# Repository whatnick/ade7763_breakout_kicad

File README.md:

# ADE7763 Breakout

Minimal Breakout Board for Analog Devices [ADE7763](https://www.analog.com/media/en/technical-documentation/data-sheets/ADE7763.pdf) Enegry Monitor ASIC. This ASIC is a bit dated, but well supported and heavily used in commercial/off-the-shelf
energy metering devices.

## Where to get it

This breakout can be obtained on:
-  [Tindie](https://www.tindie.com/products/whatnick/ade7763-breakout/) 
-  [Oshpark](https://oshpark.com/shared_projects/Y6oIkjGJ)
-  [Aisler](https://aisler.net/p/JMIMWSCE)
-  [PCBWay]()

## Usage

This PCB is designed for breadboard usage and as such should never be connected to LV (240v/120v) power. Use a transformer +
voltage divider mechanism to sample the voltage and a current transformer + multiplier resistor mechanism to sample to current.

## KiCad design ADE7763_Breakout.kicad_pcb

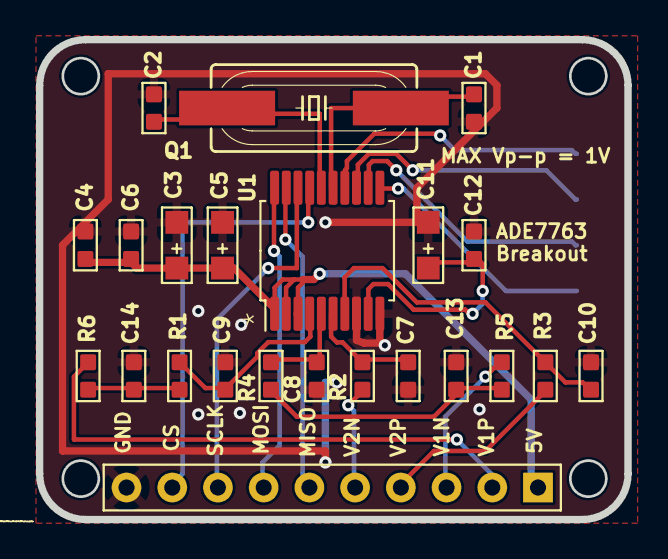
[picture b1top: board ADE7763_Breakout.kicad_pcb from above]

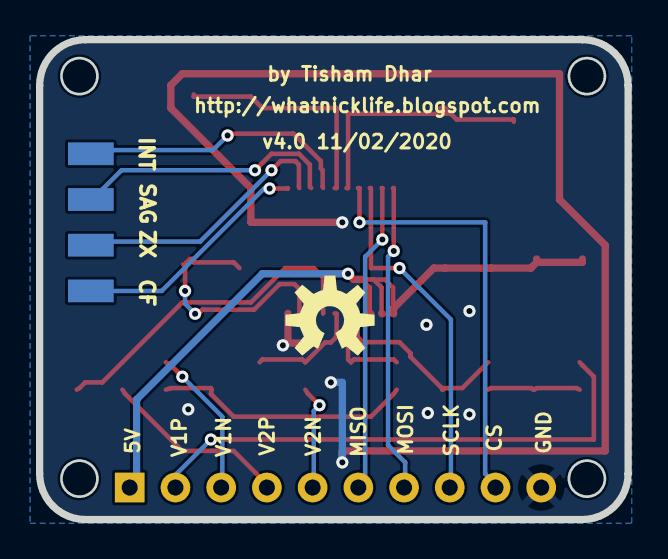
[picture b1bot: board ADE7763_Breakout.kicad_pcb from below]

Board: 2 copper layers, 32.7 x 26.7 mm, 28 parts (5 on the bottom side), 23 nets.

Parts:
C1, C2: 27p; C0603
C3, C5, C11: 10u; AVX-A
C4, C6, C12: 100n; C0603
C7, C8, C9, C10, C13, C14: 33n; C0603
CF: WIREPADSMD1,27-254; SMD1,27-2,54
INT: WIREPADSMD1,27-254; SMD1,27-2,54
J1: 10p-2.54; H10-2.54
LOGO1: OSHW-LOGOM; OSHW-LOGO-M
Q1: 3.58MHz; HC49UP
R1, R2, R3, R4: 1K; R0603
R5, R6: 100; R0603
SAG: WIREPADSMD1,27-254; SMD1,27-2,54
U1: ADE7763ARSZSSOP20; SSOP-20_5.3x7.2mm_P0.65mm
ZX: WIREPADSMD1,27-254; SMD1,27-2,54

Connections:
5V: C3.+, C4.2, C5.+, C6.2, J1.1, U1.1, U1.2, U1.3
AGND: C1.2, C2.2, C3.-, C4.1, C5.-, C6.1, C7.1, C8.1, C9.1, C10.1, C11.-, C12.1, C13.1, C14.1, J1.10, U1.8, U1.10
CLKIN: C1.1, Q1.1, U1.15
CLKOUT: C2.1, Q1.2, U1.16
CS: J1.9, U1.17
MISO: J1.6, U1.19
MOSI: J1.7, U1.20
unnamed: C13.2, R4.1, R5.1
unnamed: C14.2, R1.1, R6.1
unnamed: INT.1, U1.14
unnamed: C7.2, R2.2, U1.6
unnamed: C8.2, R4.2, U1.5
unnamed: C10.2, R3.2, U1.7
unnamed: C9.2, R1.2, U1.4
unnamed: SAG.1, U1.13
unnamed: C11.+, C12.2, U1.9
unnamed: U1.12, ZX.1
unnamed: CF.1, U1.11
SCLK: J1.8, U1.18
V1N: J1.3, R5.2
V1P: J1.2, R6.2
V2N: J1.5, R2.1
V2P: J1.4, R3.1

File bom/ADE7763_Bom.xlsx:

| References | manf# | Value | Footprint | Quantity
1 | C3, C5, C11 | TAJA106K010RNJV | 10u | AVX-A | 3
2 | R1, R2, R3, R4 | RT0603FRD071KL | 1K | R0603 | 4
3 | R5, R6 | RT0603FRD07100RL | 100 | R0603 | 2
4 | C4, C6, C12 | GCJ188R71H104KA12D | 100n | C0603 | 3
5 | C7, C8, C9, C10, C13, C14 | C0603C333K5RACTU | 33n | C0603 | 6
6 | C1, C2 | C0603C270K5GACTU | 27p | C0603 | 2
7 | U1 | ADE7763ARSZ | ADE7763ARSZSSOP20 | RS_20-M | 1
8 | Q1 | ABLS-3.579545MHZ-B4-T | 3.58MHz | HC49UP | 1
 |  |  |  |  | 22

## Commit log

2020-02-06 Initial import from Eagle
2020-02-06 Add ignore for temp/backup files
2020-02-06 Start fixing up imports and sourcing parts
2020-02-06 Add readme
2020-02-10 Complete BOM
2020-02-10 Bump version number
2020-02-11 Prevent bridging across SMD pins
2020-02-11 Close the loop on Oshpark Board
2020-05-16 Add new version to Aisler
2020-05-16 Reformat sources of PCB
2021-08-15 Start updating to sync with kicad better
2021-09-12 Fix PCB for footprint and DRC
